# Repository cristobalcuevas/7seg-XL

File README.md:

# 7seg-XL

## Front Layer

## Back Layer

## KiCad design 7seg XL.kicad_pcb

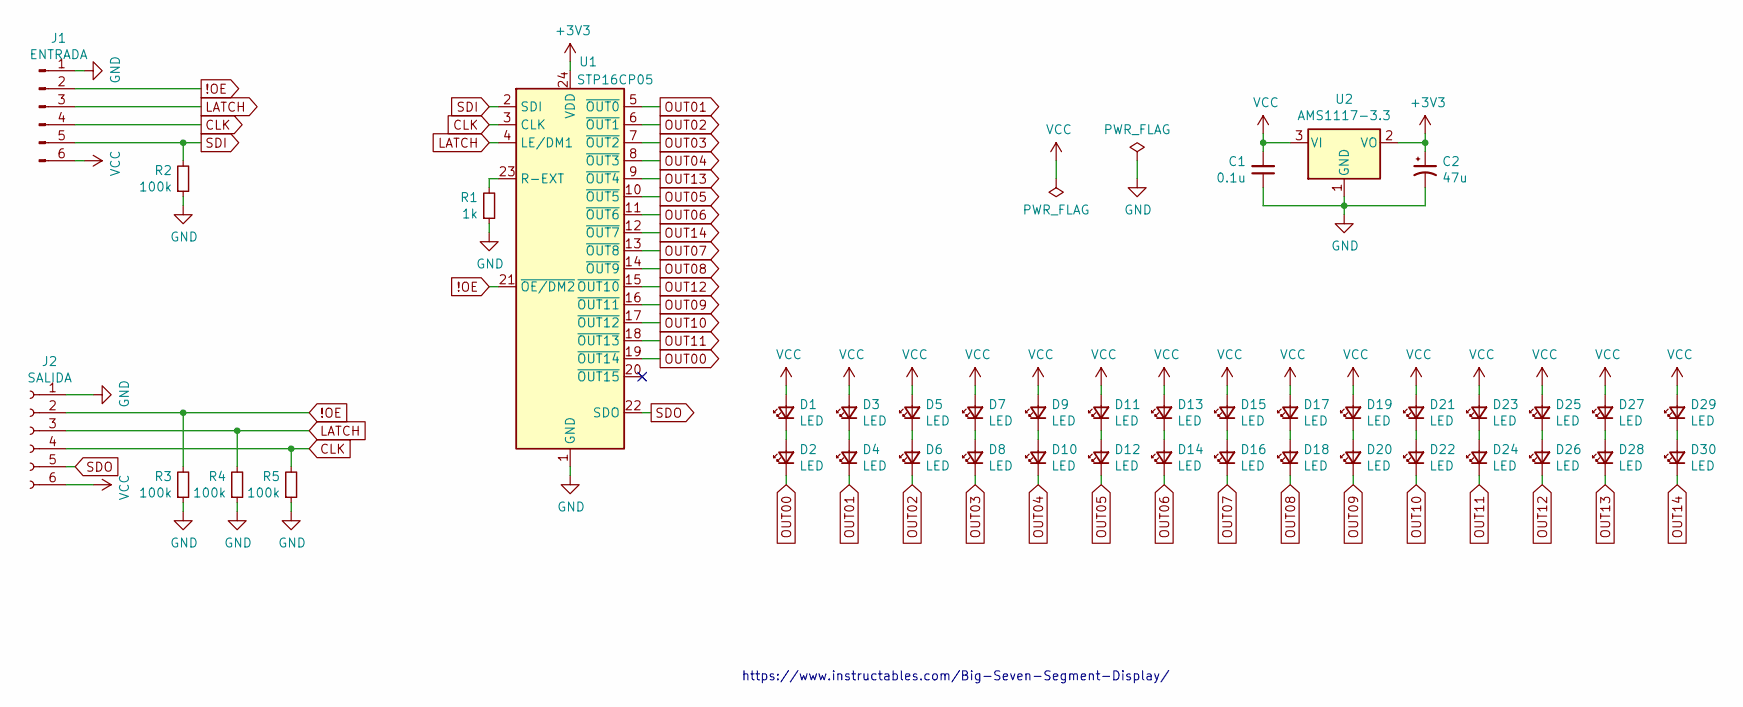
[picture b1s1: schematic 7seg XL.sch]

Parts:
C1: 0.1u; C_1206_3216Metric
C2: 47u; CP_Elec_5x5.4
D1, D2, D3, D4, D5, D6, D7, D8, D9, D10, D11, D12, D13, D14, D15, D16, D17, D18, D19, D20, D21, D22, D23, D24, D25, D26, D27, D28, D29, D30: LED; LED_2010_5025Metric_Castellated
J1: ENTRADA; PinHeader_1x06_P2.54mm_Horizontal
J2: SALIDA; PinSocket_1x06_P2.54mm_Horizontal
R1: 1k; R_1206_3216Metric
R2, R3, R4, R5: 100k; R_1206_3216Metric
U1: STP16CP05; TSSOP-24_4.4x7.8mm_P0.65mm
U2: AMS1117-3.3; SOT-223-3_TabPin2

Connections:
!OE: J1.2, J2.2, R3.2, U1.21 (~OE/DM2)
+3V3: C2.1, U1.24 (VDD), U2.2 (VO)
CLK: J1.4, J2.4, R5.2, U1.3 (CLK)
GND: C1.1, C2.2, J1.1, J2.1, R1.1, R2.1, R3.1, R4.1, R5.1, U1.1 (GND), U2.1 (GND)
LATCH: J1.3, J2.3, R4.2, U1.4 (LE/DM1)
unnamed: D1.1 (K), D2.2 (A)
unnamed: D3.1 (K), D4.2 (A)
unnamed: D5.1 (K), D6.2 (A)
unnamed: D7.1 (K), D8.2 (A)
unnamed: D9.1 (K), D10.2 (A)
unnamed: D11.1 (K), D12.2 (A)
unnamed: D13.1 (K), D14.2 (A)
unnamed: D15.1 (K), D16.2 (A)
unnamed: D17.1 (K), D18.2 (A)
unnamed: D19.1 (K), D20.2 (A)
unnamed: D21.1 (K), D22.2 (A)
unnamed: D23.1 (K), D24.2 (A)
unnamed: D25.1 (K), D26.2 (A)
unnamed: D27.1 (K), D28.2 (A)
unnamed: D29.1 (K), D30.2 (A)
unnamed: R1.2, U1.23 (R-EXT)
OUT00: D2.1 (K), U1.19 (~OUT14)
OUT01: D4.1 (K), U1.5 (~OUT0)
OUT02: D6.1 (K), U1.6 (~OUT1)
OUT03: D8.1 (K), U1.7 (~OUT2)
OUT04: D10.1 (K), U1.8 (~OUT3)
OUT05: D12.1 (K), U1.10 (~OUT5)
OUT06: D14.1 (K), U1.11 (~OUT6)
OUT07: D16.1 (K), U1.13 (~OUT8)
OUT08: D18.1 (K), U1.14 (~OUT9)
OUT09: D20.1 (K), U1.16 (~OUT11)
OUT10: D22.1 (K), U1.17 (~OUT12)
OUT11: D24.1 (K), U1.18 (~OUT13)
OUT12: D26.1 (K), U1.15 (~OUT10)
OUT13: D28.1 (K), U1.9 (~OUT4)
OUT14: D30.1 (K), U1.12 (~OUT7)
SDI: J1.5, R2.2, U1.2 (SDI)
SDO: J2.5, U1.22 (SDO)
VCC: C1.2, D1.2 (A), D3.2 (A), D5.2 (A), D7.2 (A), D9.2 (A), D11.2 (A), D13.2 (A), D15.2 (A), D17.2 (A), D19.2 (A), D21.2 (A), D23.2 (A), D25.2 (A), D27.2 (A), D29.2 (A), J1.6, J2.6, U2.3 (VI)

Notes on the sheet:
https://www.instructables.com/Big-Seven-Segment-Display/

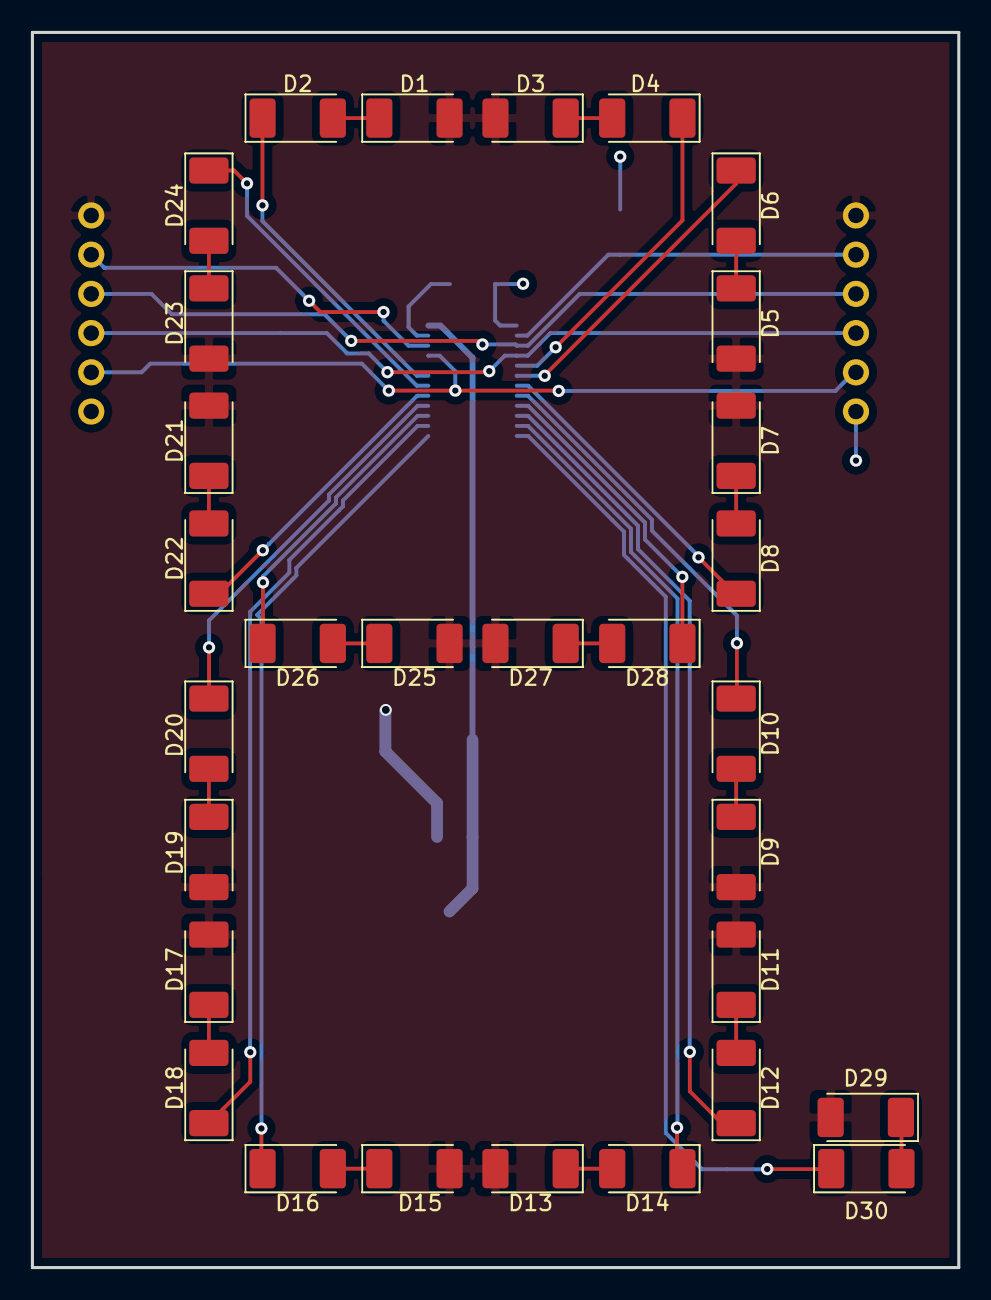
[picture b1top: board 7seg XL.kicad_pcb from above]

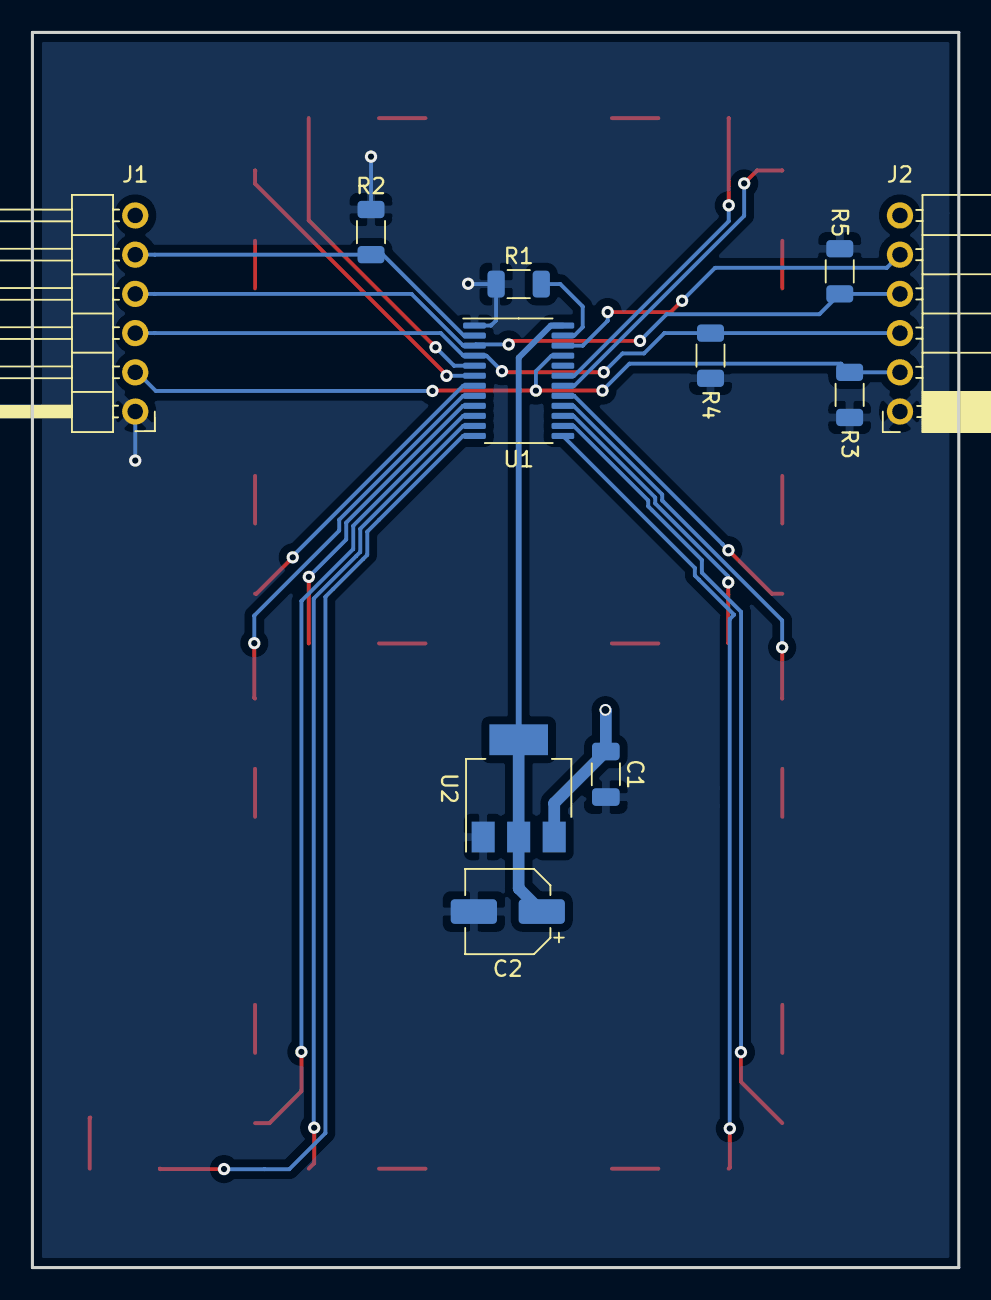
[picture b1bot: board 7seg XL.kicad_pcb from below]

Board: 2 copper layers, 60.0 x 80.0 mm, 41 parts (11 on the bottom side), 39 nets.

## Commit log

2021-04-23 version 1
